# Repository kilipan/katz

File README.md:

# katz
A minimal Y-spacing QAZ-ish board with some funny zone-fills instead of tracks and a somewhat removable spacebar in case you need to optimize the x/y ratio even further.

UNTESTED HARDWARE! MANUFACTURE AT YOUR OWN RISK!

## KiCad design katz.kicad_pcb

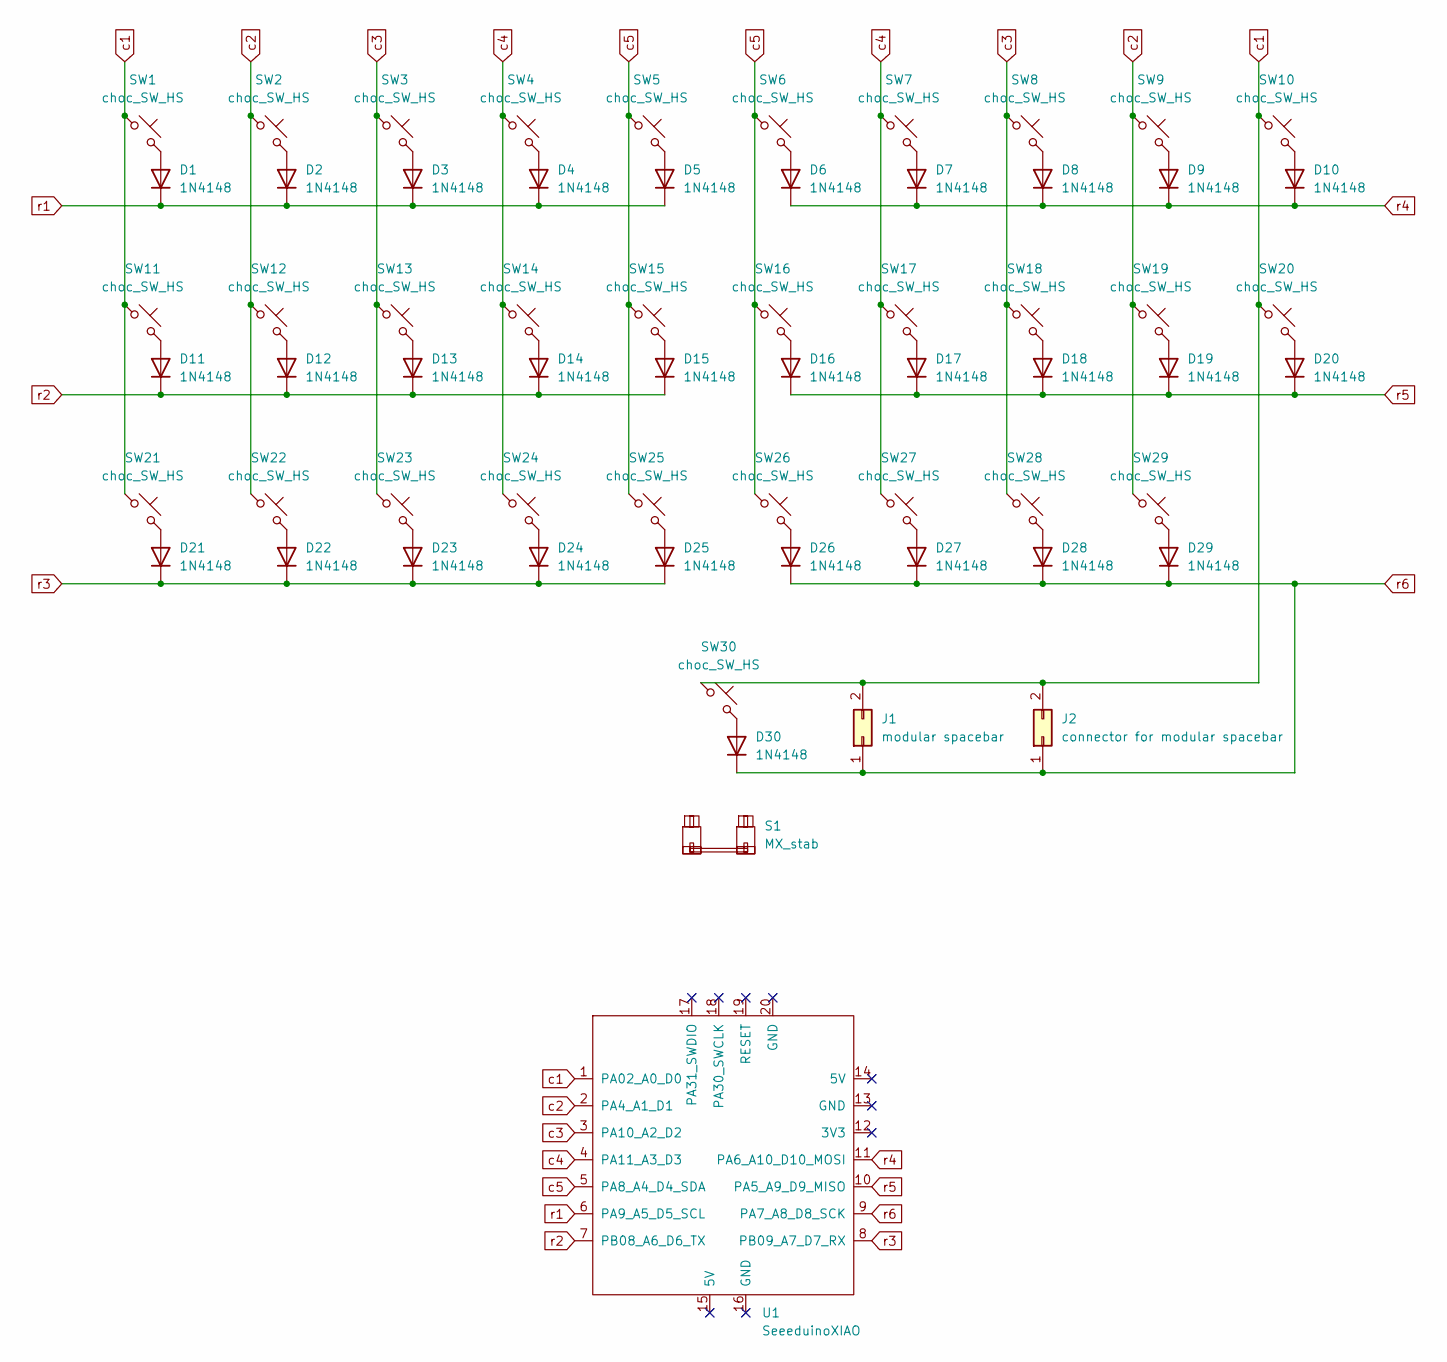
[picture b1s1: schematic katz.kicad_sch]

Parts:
D1, D2, D3, D4, D5, D6, D7, D8, D9, D10, D11, D12, D13, D14, D15, D16, D17, D18, D19, D20, D21, D22, D23, D24, D25, D26, D27, D28, D29, D30: 1N4148; D_1206_3216Metric_Pad1.42x1.75mm_HandSolder_nosilk
J1: modular spacebar; PinHeader_2x01_P2.54mm_Vertical
J2: connector for modular spacebar; PinHeader_2x01_P2.54mm_Vertical
S1: MX_stab; STAB_MX_P_6.25u
SW1, SW2, SW3, SW4, SW5, SW6, SW7, SW8, SW9, SW10, SW11, SW12, SW13, SW14, SW15, SW16, SW17, SW18, SW19, SW20, SW21, SW22, SW23, SW24, SW25, SW26, SW27, SW28, SW29, SW30: choc_SW_HS; apfel_SW_MX_solder_choc_hotswap_nosilk
U1: SeeeduinoXIAO; apfel-xiao-tht

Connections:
unnamed: D1.2 (A), SW1.2
unnamed: D2.2 (A), SW2.2
unnamed: D3.2 (A), SW3.2
unnamed: D4.2 (A), SW4.2
unnamed: D5.2 (A), SW5.2
unnamed: D6.2 (A), SW6.2
unnamed: D7.2 (A), SW7.2
unnamed: D8.2 (A), SW8.2
unnamed: D9.2 (A), SW9.2
unnamed: D10.2 (A), SW10.2
unnamed: D11.2 (A), SW11.2
unnamed: D12.2 (A), SW12.2
unnamed: D13.2 (A), SW13.2
unnamed: D14.2 (A), SW14.2
unnamed: D15.2 (A), SW15.2
unnamed: D16.2 (A), SW16.2
unnamed: D17.2 (A), SW17.2
unnamed: D18.2 (A), SW18.2
unnamed: D19.2 (A), SW19.2
unnamed: D20.2 (A), SW20.2
unnamed: D21.2 (A), SW21.2
unnamed: D22.2 (A), SW22.2
unnamed: D23.2 (A), SW23.2
unnamed: D24.2 (A), SW24.2
unnamed: D25.2 (A), SW25.2
unnamed: D26.2 (A), SW26.2
unnamed: D27.2 (A), SW27.2
unnamed: D28.2 (A), SW28.2
unnamed: D29.2 (A), SW29.2
unnamed: D30.2 (A), SW30.2
c1: J1.2, J2.2, SW1.1, SW10.1, SW11.1, SW20.1, SW21.1, SW30.1, U1.1 (PA02_A0_D0)
c2: SW2.1, SW9.1, SW12.1, SW19.1, SW22.1, SW29.1, U1.2 (PA4_A1_D1)
c3: SW3.1, SW8.1, SW13.1, SW18.1, SW23.1, SW28.1, U1.3 (PA10_A2_D2)
c4: SW4.1, SW7.1, SW14.1, SW17.1, SW24.1, SW27.1, U1.4 (PA11_A3_D3)
c5: SW5.1, SW6.1, SW15.1, SW16.1, SW25.1, SW26.1, U1.5 (PA8_A4_D4_SDA)
r1: D1.1 (K), D2.1 (K), D3.1 (K), D4.1 (K), D5.1 (K), U1.6 (PA9_A5_D5_SCL)
r2: D11.1 (K), D12.1 (K), D13.1 (K), D14.1 (K), D15.1 (K), U1.7 (PB08_A6_D6_TX)
r3: D21.1 (K), D22.1 (K), D23.1 (K), D24.1 (K), D25.1 (K), U1.8 (PB09_A7_D7_RX)
r4: D6.1 (K), D7.1 (K), D8.1 (K), D9.1 (K), D10.1 (K), U1.11 (PA6_A10_D10_MOSI)
r5: D16.1 (K), D17.1 (K), D18.1 (K), D19.1 (K), D20.1 (K), U1.10 (PA5_A9_D9_MISO)
r6: D26.1 (K), D27.1 (K), D28.1 (K), D29.1 (K), D30.1 (K), J1.1, J2.1, U1.9 (PA7_A8_D8_SCK)

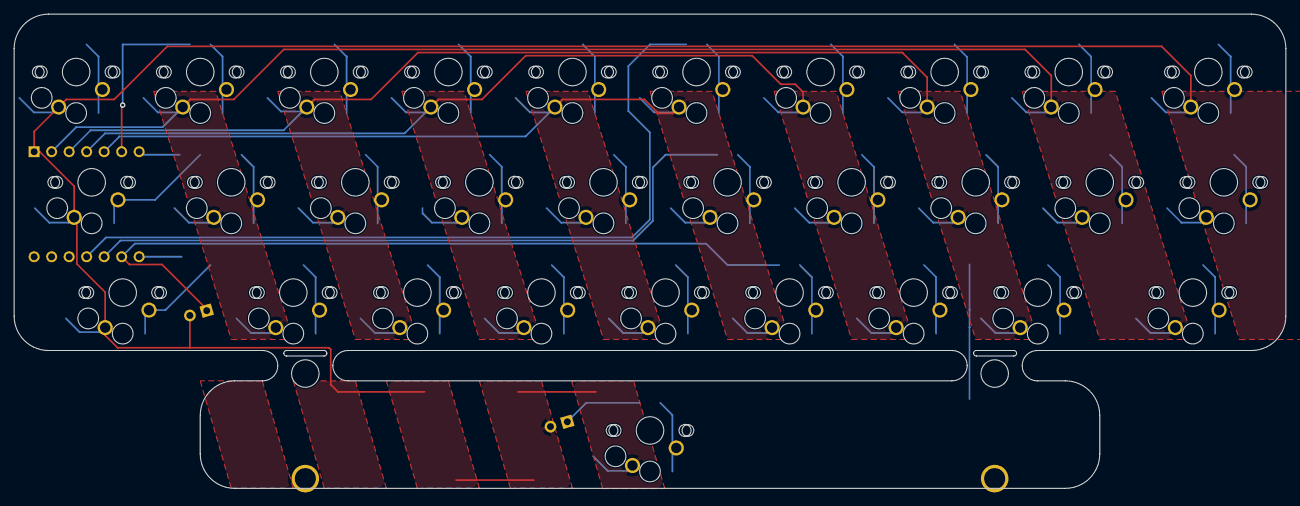
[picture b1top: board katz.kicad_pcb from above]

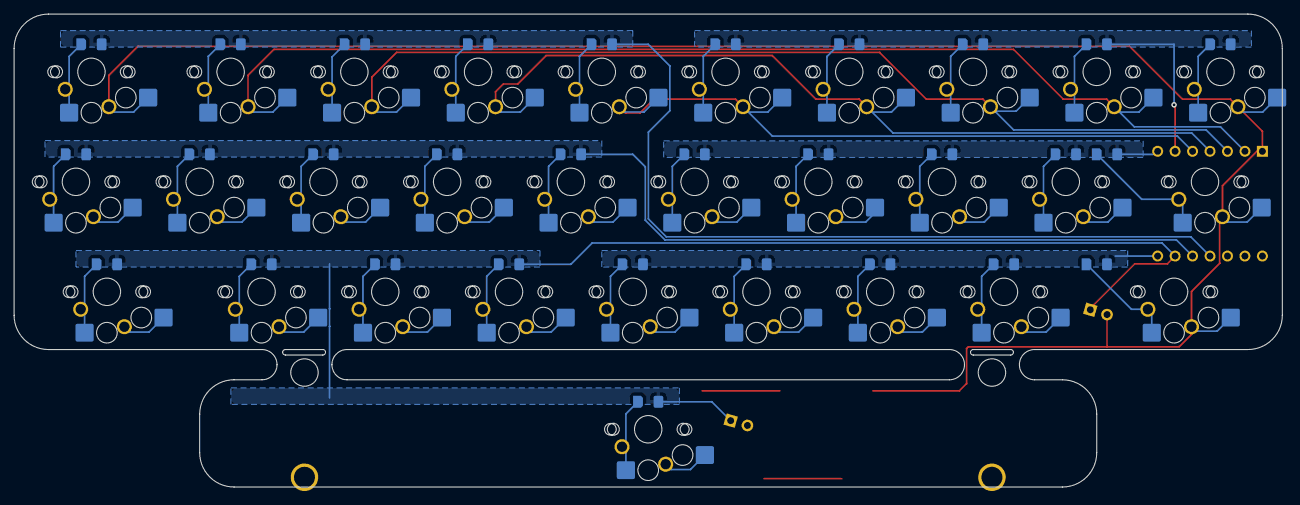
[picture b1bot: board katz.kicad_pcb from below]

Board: 2 copper layers, 184.5 x 68.8 mm, 64 parts (31 on the bottom side), 41 nets.

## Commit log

2023-10-25 add basic info to readme
2023-10-27 add pins to removable space bar
2023-10-27 add break-off cuts to space bar
2023-10-27 increase width of break-off cut
2023-12-13 add LICENSE
